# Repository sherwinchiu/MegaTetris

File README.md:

# MegaTetris
- Custom Built PCB to play Tetris on Arduino Mega
- schematic based on Arduino Mega 2560

# Hardware Needed
- Arduino Mega 2560
- 2 74HC595 (or any other serial shift register)
- 2 LCD 8x8 Matrixes
- 10 100 ohm resistors
- 5 10k ohm resistors
- 5 push buttons (4 legs)
- pin-headers for connection
- custom PCB in the file

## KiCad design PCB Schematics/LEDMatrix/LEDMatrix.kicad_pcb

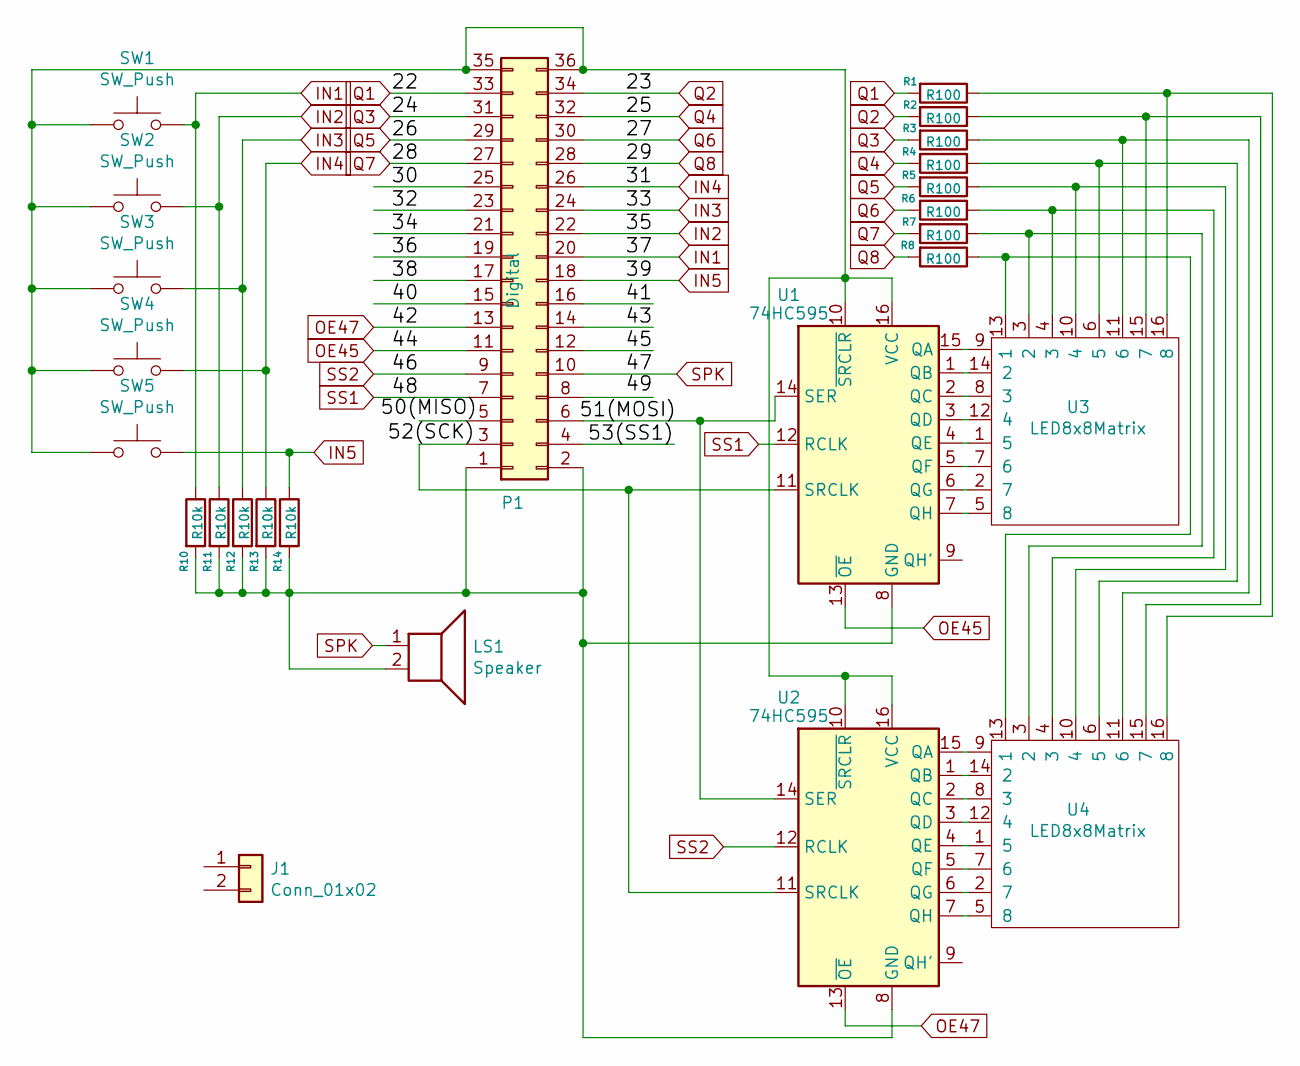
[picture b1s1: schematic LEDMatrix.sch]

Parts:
J1: Conn_01x02; PinHeader_1x02_P2.54mm_Vertical
LS1: Speaker; Buzzer_12x9.5RM7.6
P1: Digital; Socket_Strip_Arduino_2x18
R1, R2, R3, R4, R5, R6, R7, R8: R100; R_Axial_DIN0207_L6.3mm_D2.5mm_P7.62mm_Horizontal
R10, R11, R12, R13, R14: R10k; R_Axial_DIN0207_L6.3mm_D2.5mm_P7.62mm_Horizontal
SW1, SW2, SW3, SW4, SW5: SW_Push; SW_PUSH_6mm_H4.3mm
U1, U2: 74HC595; DIP-16_W7.62mm_Socket
U3, U4: LED8x8Matrix; LEDMatrix8x8

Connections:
/30: P1.25
/32: P1.23
/34: P1.21
/36: P1.19
/38: P1.17
/40: P1.15
/41: P1.16
/43: P1.14
/45: P1.12
/51(MOSI): P1.6, U1.14 (SER), U2.14 (SER)
/53(SS1): P1.4
IN1: P1.20, R10.1, SW1.2
IN2: P1.22, R11.1, SW2.2
IN3: P1.24, R12.1, SW3.2
IN4: P1.26, R13.1, SW4.2
IN5: P1.18, R14.1, SW5.2
unnamed: LS1.2, P1.1, P1.2, R10.2, R11.2, R12.2, R13.2, R14.2, U1.8 (GND), U2.8 (GND)
unnamed: P1.3, U1.11 (SRCLK), U2.11 (SRCLK)
unnamed: P1.35, P1.36, SW1.1, SW2.1, SW3.1, SW4.1, SW5.1, U1.10 (~SRCLR), U1.16 (VCC), U2.10 (~SRCLR), U2.16 (VCC)
unnamed: R1.1, U3.16 (8), U4.16 (8)
unnamed: R2.1, U3.15 (7), U4.15 (7)
unnamed: R3.1, U3.11 (6), U4.11 (6)
unnamed: R4.1, U3.6 (5), U4.6 (5)
unnamed: R5.1, U3.10 (4), U4.10 (4)
unnamed: R6.1, U3.4 (3), U4.4 (3)
unnamed: R7.1, U3.3 (2), U4.3 (2)
unnamed: R8.1, U3.13 (1), U4.13 (1)
unnamed: U1.1 (QB), U3.14 (2)
unnamed: U1.2 (QC), U3.8 (3)
unnamed: U1.3 (QD), U3.12 (4)
unnamed: U1.4 (QE), U3.1 (5)
unnamed: U1.5 (QF), U3.7 (6)
unnamed: U1.6 (QG), U3.2 (7)
unnamed: U1.7 (QH), U3.5 (8)
unnamed: U1.15 (QA), U3.9
unnamed: U2.1 (QB), U4.14 (2)
unnamed: U2.2 (QC), U4.8 (3)
unnamed: U2.3 (QD), U4.12 (4)
unnamed: U2.4 (QE), U4.1 (5)
unnamed: U2.5 (QF), U4.7 (6)
unnamed: U2.6 (QG), U4.2 (7)
unnamed: U2.7 (QH), U4.5 (8)
unnamed: U2.15 (QA), U4.9
OE45: P1.11, U1.13 (~OE)
OE47: P1.13, U2.13 (~OE)
Q1: P1.33, R1.2
Q2: P1.34, R2.2
Q3: P1.31, R3.2
Q4: P1.32, R4.2
Q5: P1.29, R5.2
Q6: P1.30, R6.2
Q7: P1.27, R7.2
Q8: P1.28, R8.2
SPK: LS1.1, P1.10
SS1: P1.7, U1.12 (RCLK)
SS2: P1.9, U2.12 (RCLK)

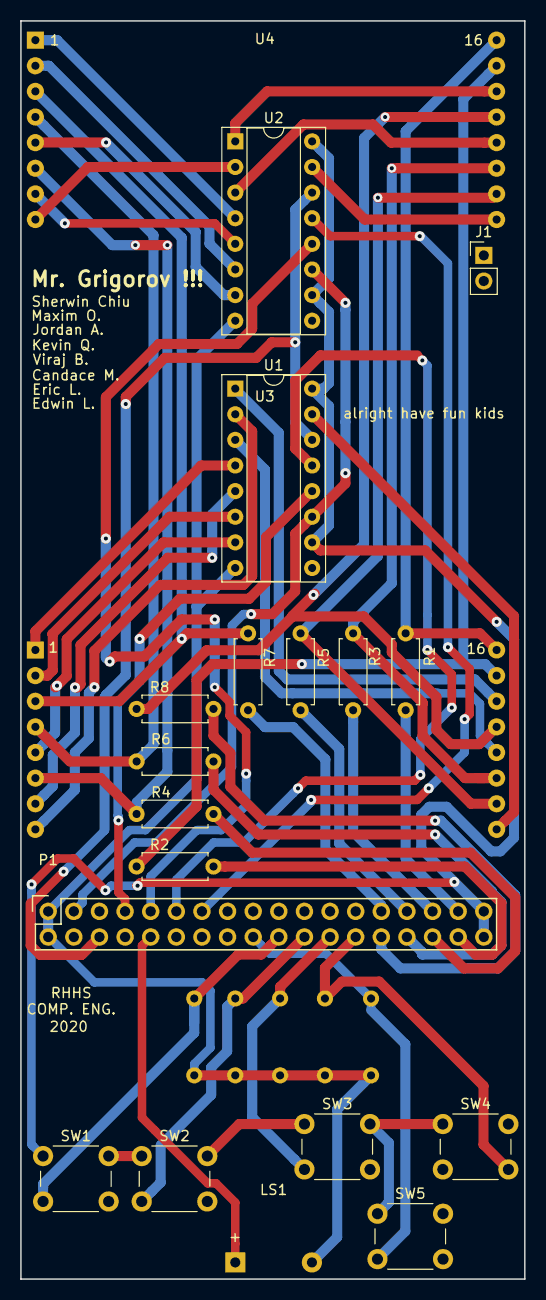
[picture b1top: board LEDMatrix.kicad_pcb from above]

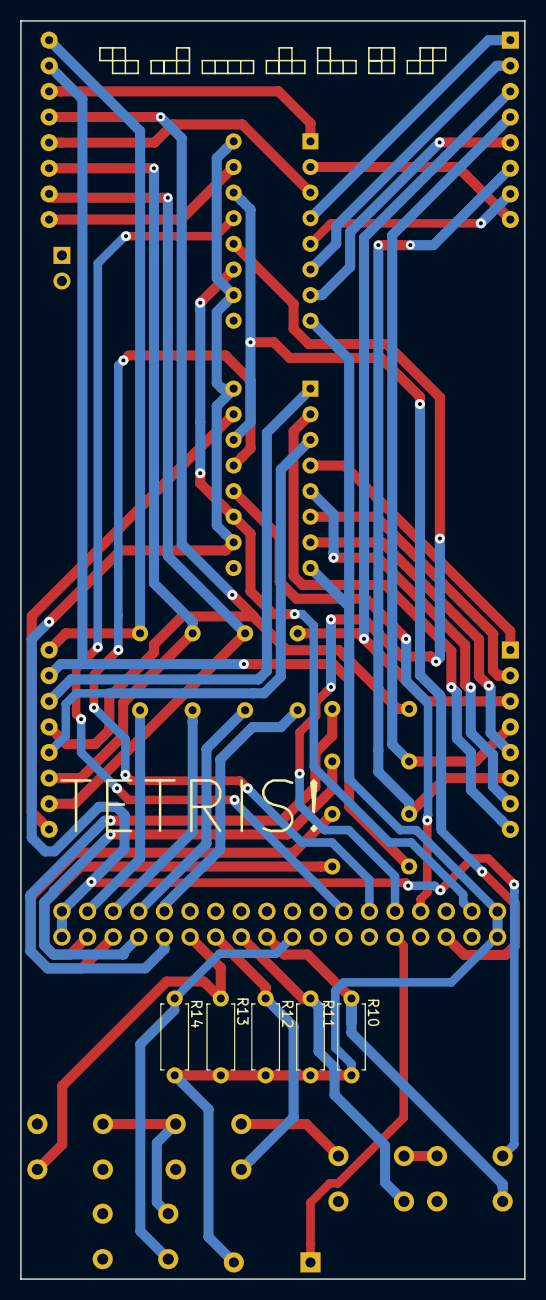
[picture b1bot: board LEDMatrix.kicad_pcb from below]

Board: 2 copper layers, 49.9 x 124.7 mm, 25 parts (5 on the bottom side), 46 nets.

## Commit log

2020-07-01 Added Tetris project
    init
    - added PCB schematic for 8x8 display
    - added Tetris code for Mega
2020-07-01 Changing README
2020-07-03 Changed pins and aded backup file
2020-07-03 Changed and updated main file
2020-07-04 Changed drawings
2020-07-04 Made movements mroe responsive
2020-07-04 Bugs with collision left to fix
2020-07-04 Need to work on sideways collision with other blocks.
2020-10-24 Updated schematic + fixed bugs
2020-10-24 clearBlcoks function works
2020-10-24 Mirrored
2020-10-25 Final Commit
